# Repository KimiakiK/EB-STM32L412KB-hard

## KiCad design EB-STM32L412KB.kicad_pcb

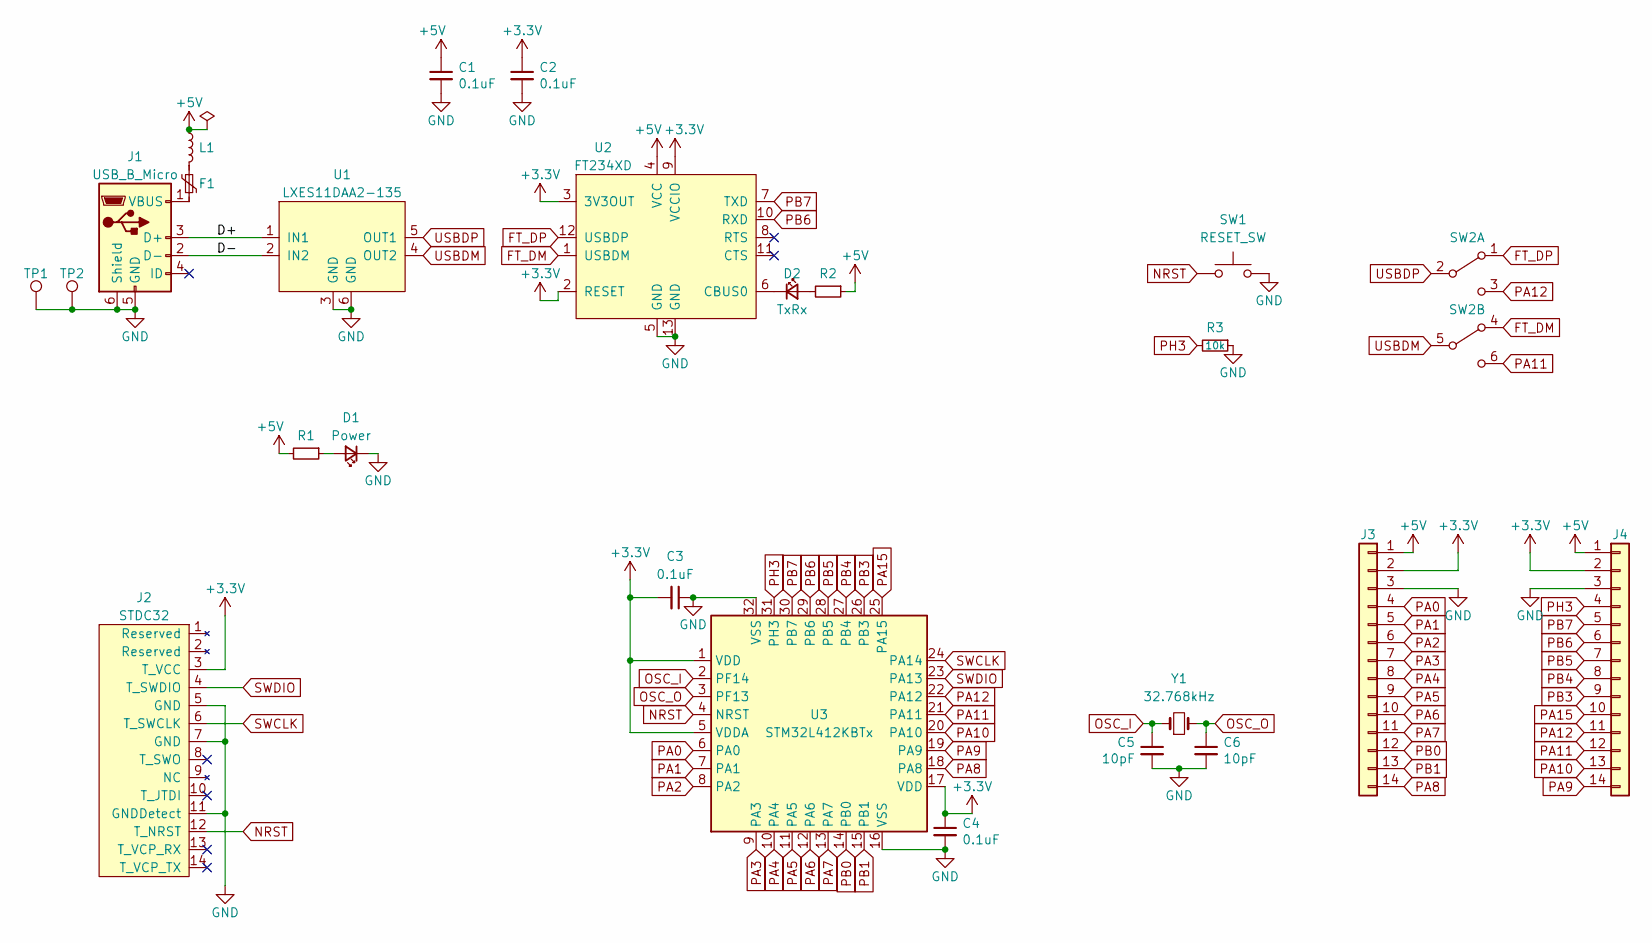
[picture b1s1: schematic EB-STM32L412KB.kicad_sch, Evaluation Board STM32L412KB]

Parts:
C1, C2, C3, C4: 0.1uF; 1608Metric
C5, C6: 10pF; 1005Metric
D1: Power; 1608Metric
D2: TxRx; 1608Metric
F1: Polyfuse_Small; 1608Metric
J1: USB_B_Micro; ZX62-B-5PA_2
J2: STDC32; BoxHeader_SMD_1.27mm_2x7pin
J3, J4: Conn_01x14; PinHeader_14pin
L1: L_Small; 1608Metric
R1, R2: R_LED; 1608Metric
R3: 10k; 1608Metric
SW1: RESET_SW; SW_TVAF06
SW2: SW_DPDT; IS-2235-G
TP1, TP2: TestPoint; TestPoint_THTPad_1.6x1.6mm_Drill1.0mm
U1: LXES11DAA2-135; LXES11D
U2: FT234XD; DFN-12-1EP_3x3mm_P0.45mm_EP1.66x2.38mm
U3: STM32L412KBTx; QFN-32-1EP_5x5mm_P0.5mm_EP3.3x3.3mm
Y1: 32.768kHz; Crystal_SMD_3215-2Pin

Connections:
+3.3V: C2.1, C3.2, C4.1, J2.3 (T_VCC), J3.2, J4.2, U2.2 (RESET), U2.3 (3V3OUT), U2.9 (VCCIO), U3.1 (VDD), U3.5 (VDDA), U3.17 (VDD)
+5V: C1.1, J3.1, J4.1, L1.1, R1.2, R2.1, U2.4 (VCC)
/D+: J1.3 (D+), U1.1 (IN1)
/D-: J1.2 (D-), U1.2 (IN2)
FT_DM: SW2.4 (A), U2.1 (USBDM)
FT_DP: SW2.1 (A), U2.12 (USBDP)
GND: C1.2, C2.2, C3.1, C4.2, C5.2, C6.2, D1.1 (K), J1.5 (GND), J1.6 (Shield), J2.5 (GND), J2.7 (GND), J2.11 (GNDDetect), J3.3, J4.3, R3.1, SW1.2, TP1.1, TP2.1, U1.3 (GND), U1.6 (GND), U2.5 (GND), U2.13 (GND), U3.16 (VSS), U3.32 (VSS)
NRST: J2.12 (T_NRST), SW1.1, U3.4 (NRST)
unnamed: D1.2 (A), R1.1
unnamed: D2.1 (K), U2.6 (CBUS0)
unnamed: D2.2 (A), R2.2
unnamed: F1.1, L1.2
unnamed: F1.2, J1.1 (VBUS)
OSC_I: C5.1, U3.2 (PF14), Y1.1
OSC_O: C6.1, U3.3 (PF13), Y1.2
PA0: J3.4, U3.6 (PA0)
PA1: J3.5, U3.7 (PA1)
PA2: J3.6, U3.8 (PA2)
PA3: J3.7, U3.9 (PA3)
PA4: J3.8, U3.10 (PA4)
PA5: J3.9, U3.11 (PA5)
PA6: J3.10, U3.12 (PA6)
PA7: J3.11, U3.13 (PA7)
PA8: J3.14, U3.18 (PA8)
PA9: J4.14, U3.19 (PA9)
PA10: J4.13, U3.20 (PA10)
PA11: J4.12, SW2.6 (C), U3.21 (PA11)
PA12: J4.11, SW2.3 (C), U3.22 (PA12)
PA15: J4.10, U3.25 (PA15)
PB0: J3.12, U3.14 (PB0)
PB1: J3.13, U3.15 (PB1)
PB3: J4.9, U3.26 (PB3)
PB4: J4.8, U3.27 (PB4)
PB5: J4.7, U3.28 (PB5)
PB6: J4.6, U2.10 (RXD), U3.29 (PB6)
PB7: J4.5, U2.7 (TXD), U3.30 (PB7)
PH3: J4.4, R3.2, U3.31 (PH3)
SWCLK: J2.6 (T_SWCLK), U3.24 (PA14)
SWDIO: J2.4 (T_SWDIO), U3.23 (PA13)
USBDM: SW2.5 (B), U1.4 (OUT2)
USBDP: SW2.2 (B), U1.5 (OUT1)

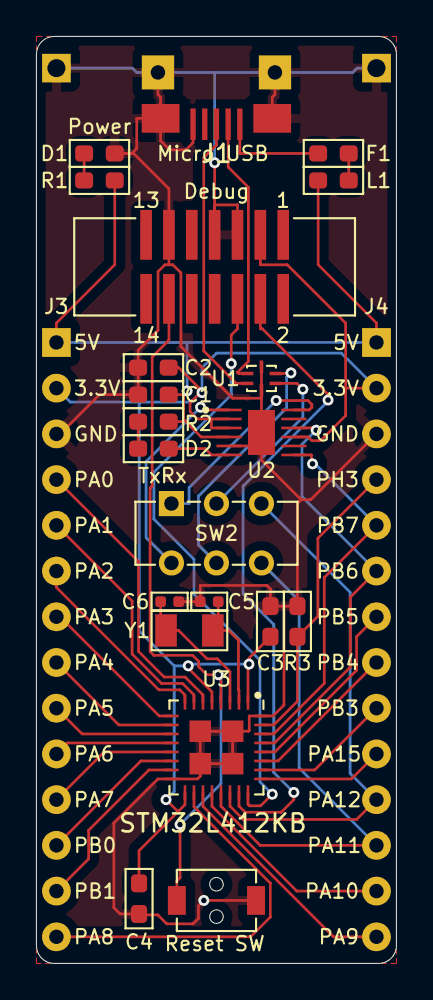
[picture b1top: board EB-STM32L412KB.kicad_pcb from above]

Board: 2 copper layers, 20.0 x 51.5 mm, 25 parts (0 on the bottom side), 41 nets.

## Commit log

2021-06-20 基板 V1.0
2022-12-10 基盤V2.0
